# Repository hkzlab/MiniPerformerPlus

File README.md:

# MiniPerformer+

## DISCLAIMER

Any use of this project is **under your own responsibility**.
You will be responsible of checking the correct construction and functionality of your board.
By using this project You will agree that I cannot be held responsible if it will destroy any of your devices, damage your computer, burn down your house or whatever.

## Introduction

This board is a remix of the [Micromac Performer](https://github.com/TheRealBolle/Performer-SE-PL-CL) reversed by Bolle,
resized for installation on the Macintosh Plus clone I am using.

Ideally, it should be usable on original Mac Pluses too, try and let me know!

### Caveat Emptor

The original Performer had a clip mounted on the underside that allowed it to snap on the motherboard's 68000 without desoldering.
Those clips are now hard to come by, so this accelerator is meant to be installed in place of the 68000, which has to be desoldered and socketed.

### Ordering the boards

You can order the board for this project at [PCBWay](https://www.pcbway.com/project/shareproject/MiniPerformer_d2c49c46.html) and support me or download 
the gerbers and have them printed wherever you like!!!

## Features

- Relatively easy to build, with socketed PLCC ICs
- ~16Mhz 68030 + optional 68882 with choice of clock source: 16Mhz internal or external oscillator

## Hardware

The board was designed with [KiCad](https://kicad.org/) EDA.

### Bill of Materials

| Component              | Qty | Type / Value                                            | Notes                                                                |
| ---------------------- | --- | ------------------------------------------------------- | -------------------------------------------------------------------- |
| R1 - R18               |  18 | 4.7k resistors, 1206                                    |                                                                      |
| C4 - C14               |  11 | 100nF/16V ceramic cap, 1206                             |                                                                      |
| C1 - C3                |  3  | 22uF/16V or 25V tantalum capacitor, 6032                |                                                                      |
| 68000 socket           |  64 | Female machined pins, >=9.7mm length                    | You can source these on AliExpress, here is an [example](https://it.aliexpress.com/item/33019740866.html). |
| QG1                    |  1  | DIP8 or DIP14 oscillator                                | Depending on the 68882, I had luck with frequencies ranging between 25 and 50Mhz |
| U1                     |  1  | 68030, PGA-128 package                                  | Avoid soldering the CPU to the board, use a socket!!!                |
| U2                     |  1  | 68882 FPU, optional, PLCC-68 package, requires socket   | The FPU is optional, to install it, a PLCC-68 THT socket is required |
| U3 - U6                |  4  | PLCC-20 PLDs, 16V8 compatbile, an SMD PLCC socket is required  | I tested both GAL16V8D and AMD PALCE16V8 PLDs for this        |
| U7                     |  1  | DIP-20 PLD, 16V8 compatible                             | Avoid GAL16V8D, tested ATF16V8 and PALCE16V8 without issues          |
| J3                     |  1  | 3 pin 2.54mm header strip                               | Used to switch between internal and external clock source for FPU    |

### Assembly

Start with the smallest SMD components: ceramic caps and resistors, on both sides of the board.
I usually do the 3 tantalum caps right after, then flip the board and install the 4 PLCC-20 sockets.

For the sockets, my usual approach is to snip away the bottom, apply copious flux on the PCB, align the sockets and then
apply solder, no need for hot air here. You do you though.

The nastiest part is installing the round pins in the 68000 footprint. Insert the pins from the topside of the board, then use a large flat blade screwdriver,
pushing the pins through the hole wiggling the pin completely in. Try not to hurt your fingers (like I did...) in the process.

The installed pins should look like this. Mind you, you will need pins >=9.7mm in length!

Once the rows are installed, I usually install a temporary socket on the pins to keep them in line, apply flux on the pcb, then solder every pin on the underside.
Try not to short them.

You can keep the through hole sockets and the 3 pin header last.

Once the all pins have been soldered, you can **VERY CAREFULLY** remove the holding socket. If you choose long enough pins, the accelerator will have enough clearance
at the bottom to install in the 68000 socket on the motherboard.

The PLDs must be programmed, the JED files can be found in [Bolle's repository](https://github.com/TheRealBolle/Performer-SE-PL-CL).

### How to disable the accelerator

Turn on the Macintosh Plus then, after the chime sound, hold the interrupt button, and push reset after that. After another chime sound plays, release the interrupt button.

The accelerator will be disabled until the next boot.

### Known Issues

- While used without this board, my clone Mac Plus had no issues in using a WDC 65C22 and fast OTP ROMs. With the accelerator installed, it gets a bit finicky on the parts and sometimes refuses to boot at all with those installed. Replacing the ROMs with standard 27C512 rated at around 150nS, plus using a plain old 6522 solved all the boot issues for me. No changes should be necessary on a stock Mac Plus, but let me know how it goes for you.
- Also, note that the choice of PLD type for the build is important, especially for U7: I had good luck with PALCE16V8 rated at 25ns or ATF16V8 rated at 15. Pain and tears with GAL16V8D though.
- Like the original Performer, using this accelerator could get You audio distorsion in some software

### Future Improvements

- Possibly replace U7 with a PLL for configurable speed
- A revision with a QFP 68030?

### Extra

A nice [video](https://www.youtube.com/watch?v=oIT5QKRQgww) by BigBadBiologist on how to abuse a Macintosh Classic with this board meant for a Macintosh Plus!

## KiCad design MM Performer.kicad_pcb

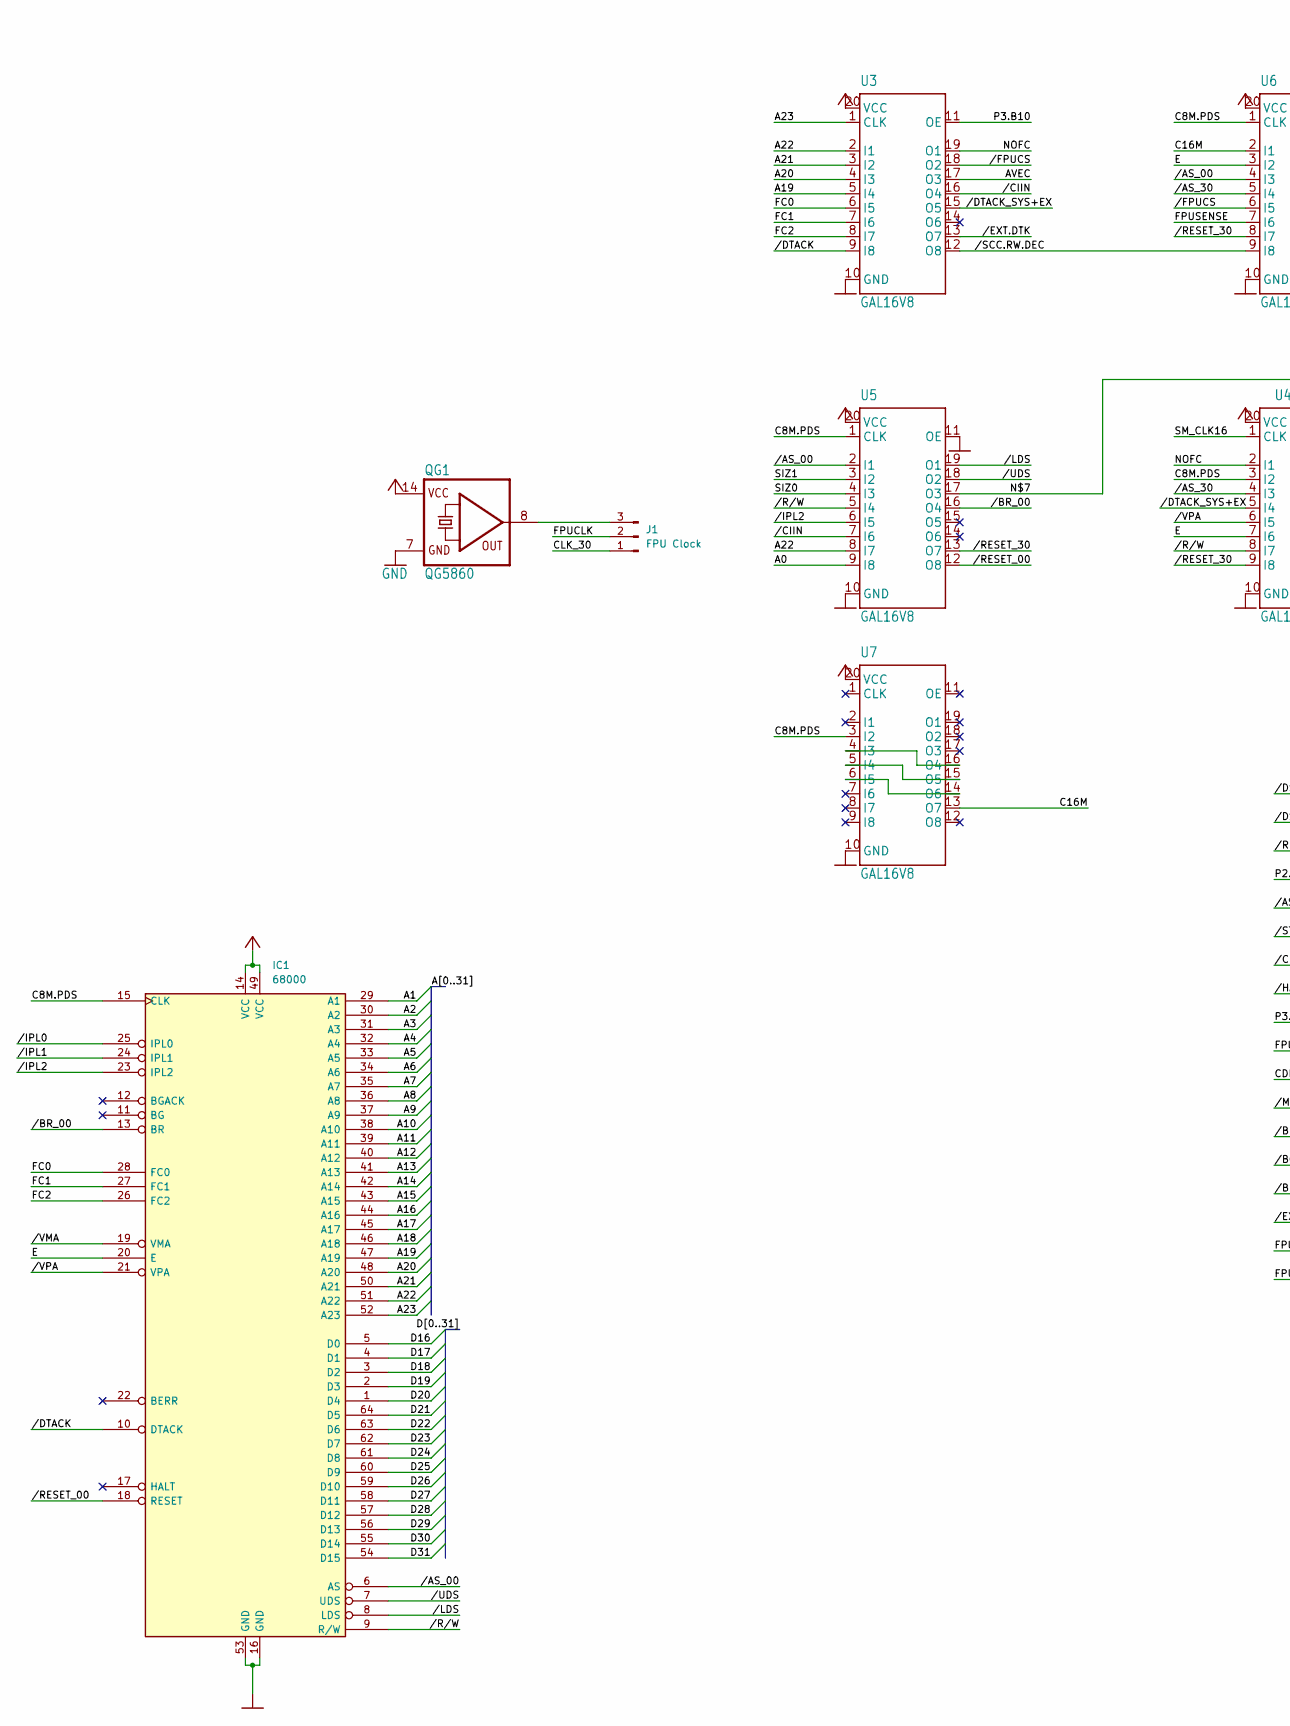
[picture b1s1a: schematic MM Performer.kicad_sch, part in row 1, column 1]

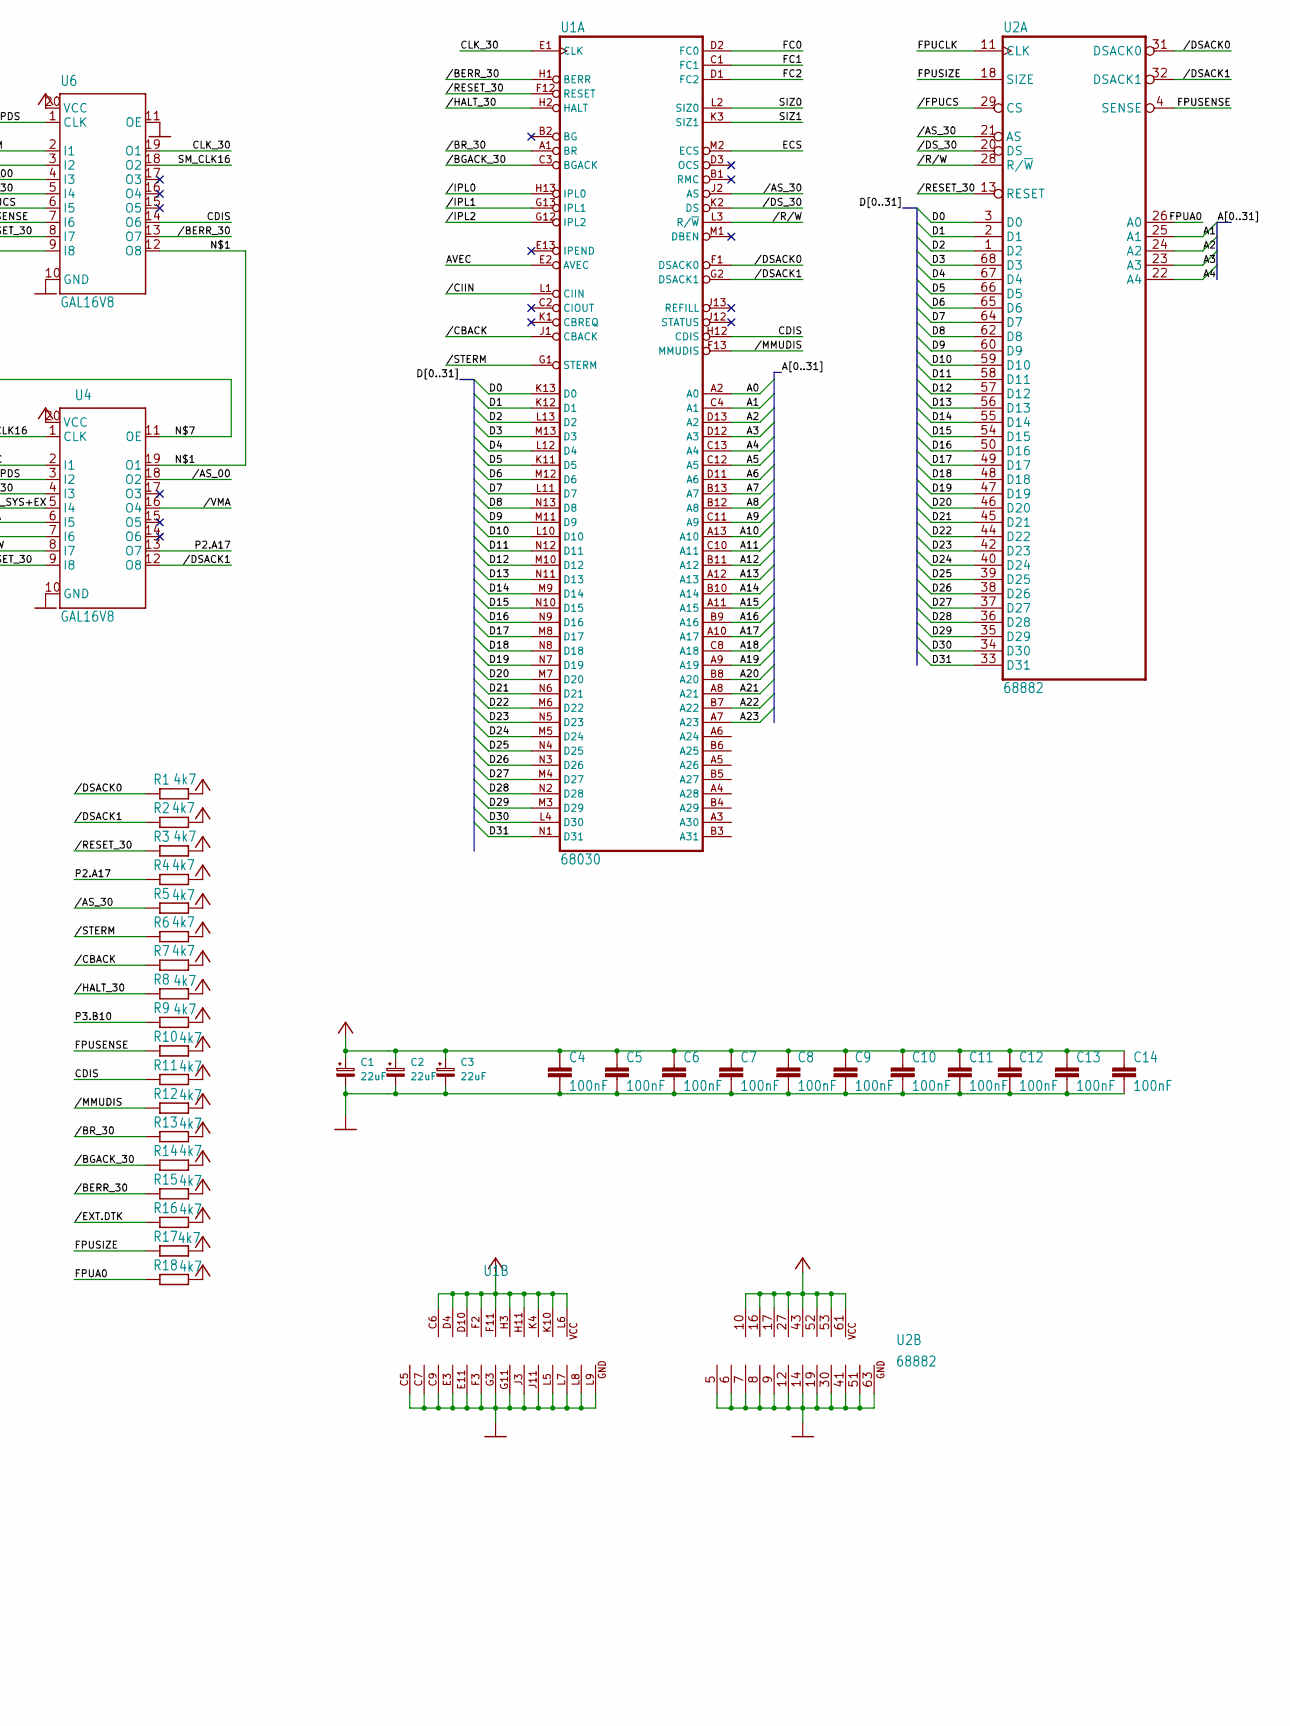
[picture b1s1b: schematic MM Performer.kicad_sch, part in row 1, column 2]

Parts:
C1, C2, C3: 22uF; CP_EIA-6032-28_Kemet-C_Pad2.25x2.35mm_HandSolder
C4, C5, C6, C7, C8, C9, C10, C11, C12, C13, C14: 100nF; C_1206_3216Metric_Pad1.33x1.80mm_HandSolder
IC1: 68000; DIP-64_W22.86mm
J1: FPU Clock; PinHeader_1x03_P2.54mm_Vertical
QG1: QG5860; Oscillator_DIP-14-8
R1, R2, R3, R4, R5, R6, R7, R8, R9, R10, R11, R12, R13, R14, R15, R16, R17, R18: 4k7; R_1206_3216Metric_Pad1.30x1.75mm_HandSolder
U1: 68030; CPGA-128_Layout13x13_MC68030
U2: 68882; PLCC-68_THT-Socket
U3, U4, U5, U6: GAL16V8; PLCC-20_SMD-Socket
U7: GAL16V8; DIP-20_W7.62mm

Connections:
/A0: U1.A2 (A0), U5.9 (I8)
/A1: IC1.29 (A1), U1.C4 (A1), U2.25 (A1)
/A2: IC1.30 (A2), U1.D13 (A2), U2.24 (A2)
/A3: IC1.31 (A3), U1.D12 (A3), U2.23 (A3)
/A4: IC1.32 (A4), U1.C13 (A4), U2.22 (A4)
/A5: IC1.33 (A5), U1.C12 (A5)
/A6: IC1.34 (A6), U1.D11 (A6)
/A7: IC1.35 (A7), U1.B13 (A7)
/A8: IC1.36 (A8), U1.B12 (A8)
/A9: IC1.37 (A9), U1.C11 (A9)
/A10: IC1.38 (A10), U1.A13 (A10)
/A11: IC1.39 (A11), U1.C10 (A11)
/A12: IC1.40 (A12), U1.B11 (A12)
/A13: IC1.41 (A13), U1.A12 (A13)
/A14: IC1.42 (A14), U1.B10 (A14)
/A15: IC1.43 (A15), U1.A11 (A15)
/A16: IC1.44 (A16), U1.B9 (A16)
/A17: IC1.45 (A17), U1.A10 (A17)
/A18: IC1.46 (A18), U1.C8 (A18)
/A19: IC1.47 (A19), U1.A9 (A19), U3.5 (I4)
/A20: IC1.48 (A20), U1.B8 (A20), U3.4 (I3)
/A21: IC1.50 (A21), U1.A8 (A21), U3.3 (I2)
/A22: IC1.51 (A22), U1.B7 (A22), U3.2 (I1), U5.8 (I7)
/A23: IC1.52 (A23), U1.A7 (A23), U3.1 (CLK)
/AVEC: U1.E2 (AVEC), U3.17 (O3)
/C8M.PDS: IC1.15 (CLK), U4.3 (I2), U5.1 (CLK), U6.1 (CLK), U7.3 (I2)
/C16M: U6.2 (I1), U7.13 (O7)
/CDIS: R11.1, U1.H12 (CDIS), U6.14 (O6)
/CLK_30: J1.1, U1.E1 (CLK), U6.19 (O1)
/D0: U1.K13 (D0), U2.3 (D0)
/D1: U1.K12 (D1), U2.2 (D1)
/D2: U1.L13 (D2), U2.1 (D2)
/D3: U1.M13 (D3), U2.68 (D3)
/D4: U1.L12 (D4), U2.67 (D4)
/D5: U1.K11 (D5), U2.66 (D5)
/D6: U1.M12 (D6), U2.65 (D6)
/D7: U1.L11 (D7), U2.64 (D7)
/D8: U1.N13 (D8), U2.62 (D8)
/D9: U1.M11 (D9), U2.60 (D9)
/D10: U1.L10 (D10), U2.59 (D10)
/D11: U1.N12 (D11), U2.58 (D11)
/D12: U1.M10 (D12), U2.57 (D12)
/D13: U1.N11 (D13), U2.56 (D13)
/D14: U1.M9 (D14), U2.55 (D14)
/D15: U1.N10 (D15), U2.54 (D15)
/D16: IC1.5 (D0), U1.N9 (D16), U2.50 (D16)
/D17: IC1.4 (D1), U1.M8 (D17), U2.49 (D17)
/D18: IC1.3 (D2), U1.N8 (D18), U2.48 (D18)
/D19: IC1.2 (D3), U1.N7 (D19), U2.47 (D19)
/D20: IC1.1 (D4), U1.M7 (D20), U2.46 (D20)
/D21: IC1.64 (D5), U1.N6 (D21), U2.45 (D21)
/D22: IC1.63 (D6), U1.M6 (D22), U2.44 (D22)
/D23: IC1.62 (D7), U1.N5 (D23), U2.42 (D23)
/D24: IC1.61 (D8), U1.M5 (D24), U2.40 (D24)
/D25: IC1.60 (D9), U1.N4 (D25), U2.39 (D25)
/D26: IC1.59 (D10), U1.N3 (D26), U2.38 (D26)
/D27: IC1.58 (D11), U1.M4 (D27), U2.37 (D27)
/D28: IC1.57 (D12), U1.N2 (D28), U2.36 (D28)
/D29: IC1.56 (D13), U1.M3 (D29), U2.35 (D29)
/D30: IC1.55 (D14), U1.L4 (D30), U2.34 (D30)
/D31: IC1.54 (D15), U1.N1 (D31), U2.33 (D31)
/E: IC1.20 (E), U4.7 (I6), U6.3 (I2)
/ECS: U1.M2 (ECS)
/FC0: IC1.28 (FC0), U1.D2 (FC0), U3.6 (I5)
/FC1: IC1.27 (FC1), U1.C1 (FC1), U3.7 (I6)
/FC2: IC1.26 (FC2), U1.D1 (FC2), U3.8 (I7)
/FPUA0: R18.1, U2.26 (A0)
/FPUCLK: J1.2, U2.11 (CLK)
/FPUSENSE: R10.1, U2.4 (SENSE), U6.7 (I6)
/FPUSIZE: R17.1, U2.18 (SIZE)
/N$1: U4.19 (O1), U6.12 (O8)
/N$7: U4.11 (OE), U5.17 (O3)
/NOFC: U3.19 (O1), U4.2 (I1)
/P2.A17: R4.1, U4.13 (O7)
/P3.B10: R9.1, U3.11 (OE)
/SIZ0: U1.L2 (SIZ0), U5.4 (I3)
/SIZ1: U1.K3 (SIZ1), U5.3 (I2)
/SM_CLK16: U4.1 (CLK), U6.18 (O2)
//AS_00: IC1.6 (AS), U4.18 (O2), U5.2 (I1), U6.4 (I3)
//AS_30: R5.1, U1.J2 (AS), U2.21 (AS), U4.4 (I3), U6.5 (I4)
//BERR_30: R15.1, U1.H1 (BERR), U6.13 (O7)
//BGACK_30: R14.1, U1.C3 (BGACK)
//BR_00: IC1.13 (BR), U5.16 (O4)
//BR_30: R13.1, U1.A1 (BR)
//CBACK: R7.1, U1.J1 (CBACK)
//CIIN: U1.L1 (CIIN), U3.16 (O4), U5.7 (I6)
//DSACK0: R1.1, U1.F1 (DSACK0), U2.31 (DSACK0)
//DSACK1: R2.1, U1.G2 (DSACK1), U2.32 (DSACK1), U4.12 (O8)
//DS_30: U1.K2 (DS), U2.20 (DS)
//DTACK: IC1.10 (DTACK), U3.9 (I8)
//DTACK_SYS+EX: U3.15 (O5), U4.5 (I4)
//EXT.DTK: R16.1, U3.13 (O7)
//FPUCS: U2.29 (CS), U3.18 (O2), U6.6 (I5)
//HALT_30: R8.1, U1.H2 (HALT)
//IPL0: IC1.25 (IPL0), U1.H13 (IPL0)
//IPL1: IC1.24 (IPL1), U1.G13 (IPL1)
//IPL2: IC1.23 (IPL2), U1.G12 (IPL2), U5.6 (I5)
//LDS: IC1.8 (LDS), U5.19 (O1)
//MMUDIS: R12.1, U1.F13 (MMUDIS)
//RESET_00: IC1.18 (RESET), U5.12 (O8)
//RESET_30: R3.1, U1.F12 (RESET), U2.13 (RESET), U4.9 (I8), U5.13 (O7), U6.8 (I7)
//R/W: IC1.9 (R/W), U1.L3 (R/~W), U2.28 (R/~W), U4.8 (I7), U5.5 (I4)
//SCC.RW.DEC: U3.12 (O8), U6.9 (I8)
//STERM: R6.1, U1.G1 (STERM)
//UDS: IC1.7 (UDS), U5.18 (O2)
//VMA: IC1.19 (VMA), U4.16 (O4)
//VPA: IC1.21 (VPA), U4.6 (I5)
GND: C1.2, C2.2, C3.2, C4.2, C5.2, C6.2, C7.2, C8.2, C9.2, C10.2, C11.2, C12.2, C13.2, C14.2, IC1.16 (GND), IC1.53 (GND), QG1.7 (GND), U1.C5 (GND@1), U1.C7 (GND@2), U1.C9 (GND@3), U1.E3 (GND@4), U1.E11 (GND@5), U1.F3 (GND@6), U1.G3 (GND@7), U1.G11 (GND@8), U1.J3 (GND@9), U1.J11 (GND@10), U1.L5 (GND@11), U1.L7 (GND@12), U1.L8 (GND@13), U1.L9 (GND@14), U2.5 (GND@1), U2.6 (GND@2), U2.7 (GND@3), U2.8 (GND@4), U2.9 (GND@5), U2.12 (GND@6), U2.14 (GND@7), U2.19 (GND@8), U2.30 (GND@9), U2.41 (GND@10), U2.51 (GND@11), U2.63 (GND@12), U3.10 (GND), U4.10 (GND), U5.10 (GND), U5.11 (OE), U6.10 (GND), U6.11 (OE), U7.10 (GND)
unnamed: J1.3, QG1.8 (OUT)
unnamed: U7.4 (I3), U7.16 (O4)
unnamed: U7.5 (I4), U7.15 (O5)
unnamed: U7.6 (I5), U7.14 (O6)
VCC: C1.1, C2.1, C3.1, C4.1, C5.1, C6.1, C7.1, C8.1, C9.1, C10.1, C11.1, C12.1, C13.1, C14.1, IC1.14 (VCC), IC1.49 (VCC), QG1.14 (VCC), R1.2, R2.2, R3.2, R4.2, R5.2, R6.2, R7.2, R8.2, R9.2, R10.2, R11.2, R12.2, R13.2, R14.2, R15.2, R16.2, R17.2, R18.2, U1.C6 (VCC@1), U1.D4 (VCC@2), U1.D10 (VCC@3), U1.F2 (VCC@4), U1.F11 (VCC@5), U1.H3 (VCC@6), U1.H11 (VCC@7), U1.K4 (VCC@8), U1.K10 (VCC@9), U1.L6 (VCC@10), U2.10 (VCC@1), U2.16 (VCC@2), U2.17 (VCC@3), U2.27 (VCC@4), U2.43 (VCC@5), U2.52 (VCC@6), U2.53 (VCC@7), U2.61 (VCC@8), U3.20 (VCC), U4.20 (VCC), U5.20 (VCC), U6.20 (VCC), U7.20 (VCC)

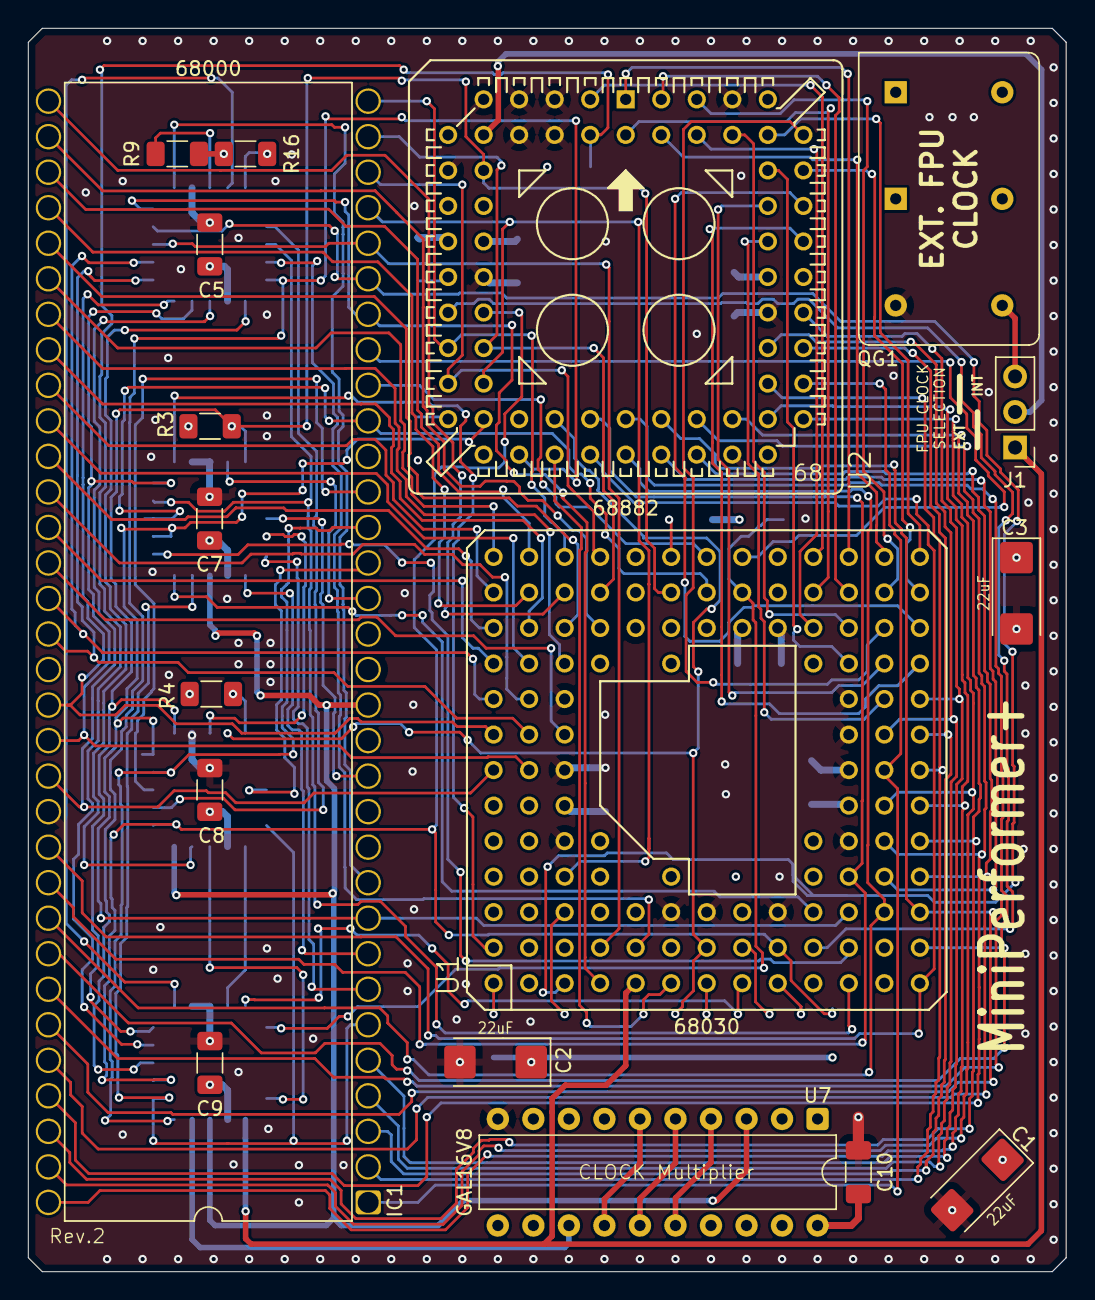
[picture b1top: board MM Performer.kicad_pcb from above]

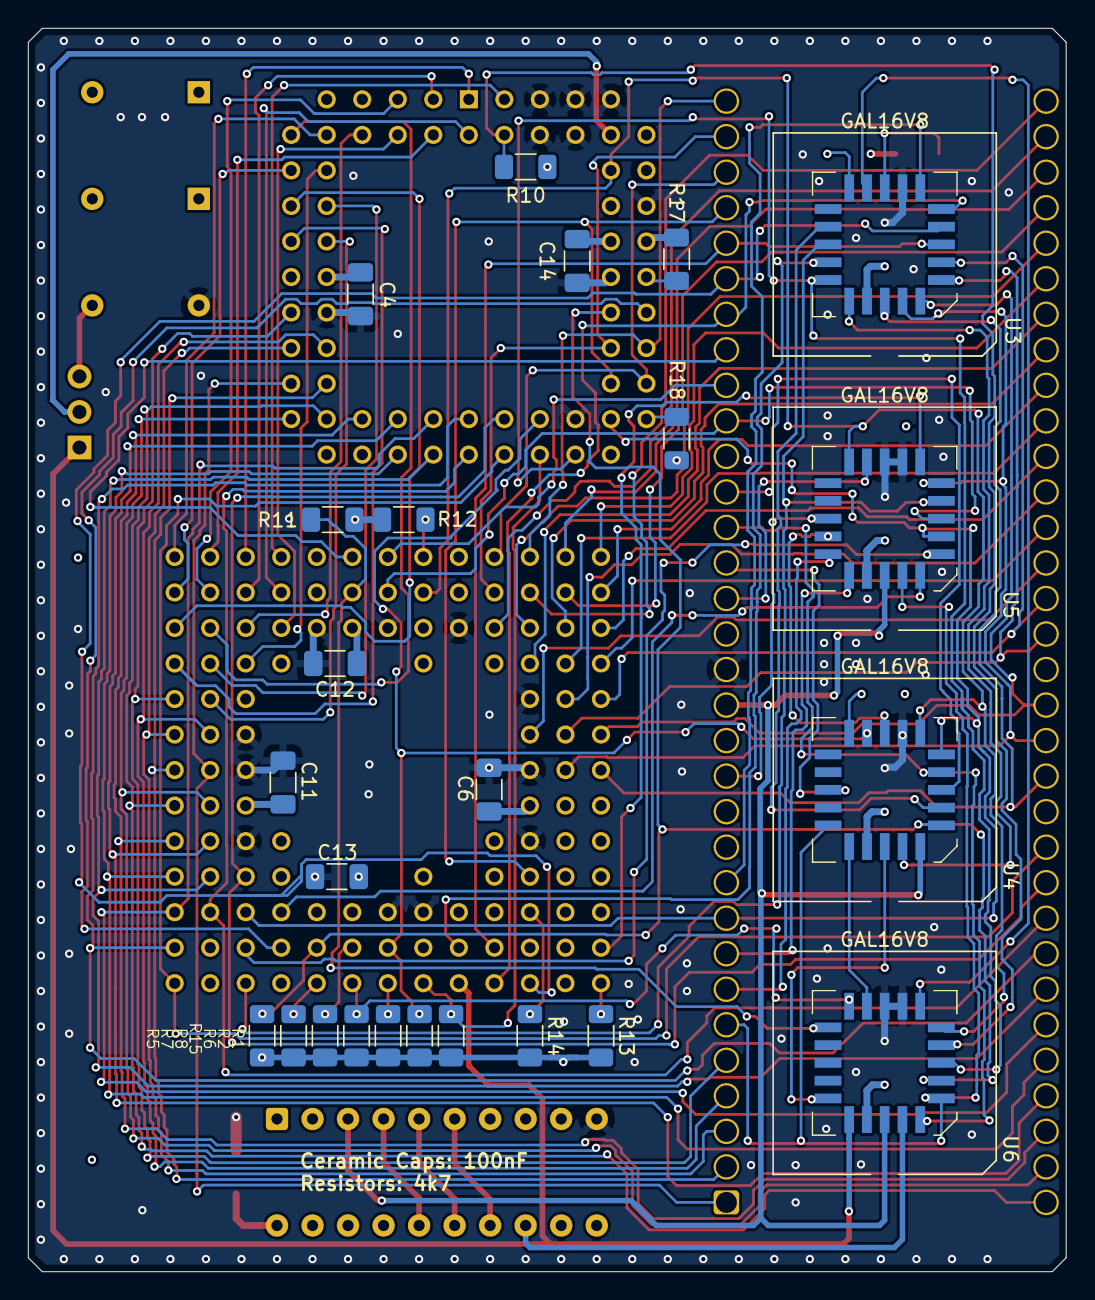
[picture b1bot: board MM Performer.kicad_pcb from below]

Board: 4 copper layers, 74.2 x 88.9 mm, 42 parts (24 on the bottom side), 112 nets.

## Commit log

2025-03-03 First import
2025-03-03 Tweak positioning a bit
2025-03-03 Reorganize a bit
2025-03-03 Reorganize the positions
2025-03-03 Current setup
2025-03-03 Performer
2025-03-03 Update footprints
2025-03-03 Draw PCB
2025-03-28 Change width of a VCC trace
2025-03-29 Cleaning up the schematic
2025-03-29 Further cleanup
2025-03-31 Begin cleanup of the traces for the new revision
2025-03-31 Reorganize placement on the PCB
2025-03-31 Reorganize the board again
2025-03-31 Initial routing of clock and power traces
2025-04-01 Some rerouting of traces
2025-04-01 Update routing
2025-04-01 Move cap near CPU
2025-04-01 Tweak the routing some more
2025-04-01 Further signal tweaks
2025-04-01 Further tweaks
2025-04-01 Tweak placement again
2025-04-01 Reposition CPU
2025-04-02 Route traces, add zones
2025-04-02 Further silkscreen changes and trace rerouting
2025-04-02 Begin fixing the autorouter's mess
2025-04-02 Further tweaks to routing
2025-04-02 Further fixes to traces
2025-04-02 Add silkscreen for caps/resistor values
2025-04-05 Generate gerbers for rev_1
2025-04-17 Moved around two resistor markings
2025-04-19 Add schematics, regenerate gerber
2025-04-19 Initial README version
2025-04-19 Update README with additional pics
2025-04-19 Add notes on future improvements to the README
2025-04-19 Further notes
2025-04-19 Additional notes on the disclaimer
2025-04-19 Additional future improvements listed
2025-04-19 Further notes and specifications in the README
2025-04-19 Whoops, it was "Mini" and not "Micro" Performer
2025-04-19 Remove section on board ordering
2025-04-19 Fixed typo
2025-04-19 Mention PCBWay for ordering boards
2025-05-14 Import revision 2 board
2025-05-14 Update the README to mention audio distorsion and fix a picture description
2025-05-15 Condensed two points under "Known Issues"
2025-06-22 Update the README
2026-03-15 Add instructions on how to disable the accelerator
2026-05-31 Additional pictures about installation
2026-05-31 Update pictures
2026-06-11 Add LICENSE
